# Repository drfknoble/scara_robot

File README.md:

# Selective Compliance Articulated Robot Arm (SCARA) Project

## Introduction

Welcome to my repository for my Selective Compliance Articulared Robot Arm (SCARA) project.

<!-- <div>

</div> -->

## Motivation

I started this project because commercial SCARA robots are very expensive and there any low-cost options for me to use in my teaching or research.

## Aims

The aims of this project included:
- Developing a low-cost, SCARA robot that can be used to teach students about mechatronics and robotics.

## Objectives

The objectives of this project included:
- Creating accessible Computer Aided Design (CAD) files.
- Creating accessible Electronics Design Automation (EDA) files.
- Creating accessible source code and software libraries.
- Creating an easy-to-assemble mobile robot that uses a microcontroller, stepper motors, and rotational sensors.

## Repository Structure

The repository is organised as follows:

```console
scara_project/         
    cad/                          
        fabrication/
        parts/
        sub_assemblies/   
    doc/                                   
    eda/
        manipulator_pcb/        
    src/
        esp32_program/
        my_bringup/
        my_scara_1_0_movit_config/
        my_scara_support/
```

All CAD files can be found in the `cad/` sub-directory. I used SolidWorks to create the 3D models of the robot's parts, sub-assemblies, and assembly. Files neeeded to fabricate the robot can be found in the `fabrication/` sub-directory.

All EDA files can be found in the `eda/` sub-directory. I used KiCAD to create the PCB for the robot. Files need to fabricate the PCB can be found in the `manipulator_pcb/` sub-directory.

All source code and software libaries are included in the `src/` sub-directory. I used an ESP32 as the robot's microcontroller and programmed it using PlatformIO's Arduino framework. The ESP32's source code can be found in the `esp32_program/` sub-directory. I also developed a ROS 2 package that makes use of ROS 2 Control and Moveit 2. The package's launch file can be found in the `my_bringup/` sub-directory. 

Documentation is included in the `doc/` sub-directory. I've included a Bill of Materaisl (BOM) file, which includes the compenents used.

## Tools Used

I used the following tools in this project:
- SOLIDWORKS.
- KiCAD.
- Microsoft Visual Studio Code and PlatforIO.
- ROS 2.

Get FreeCAD here: https://www.freecadweb.org/.  
Get KiCAD here: https://www.kicad.org/.  
Get Visual Studio Code here: https://code.visualstudio.com/.  
Get PlatforIO from here: https://platformio.org/. 

## Credit

Dr Frazer K. Noble  
http://drfknoble.com

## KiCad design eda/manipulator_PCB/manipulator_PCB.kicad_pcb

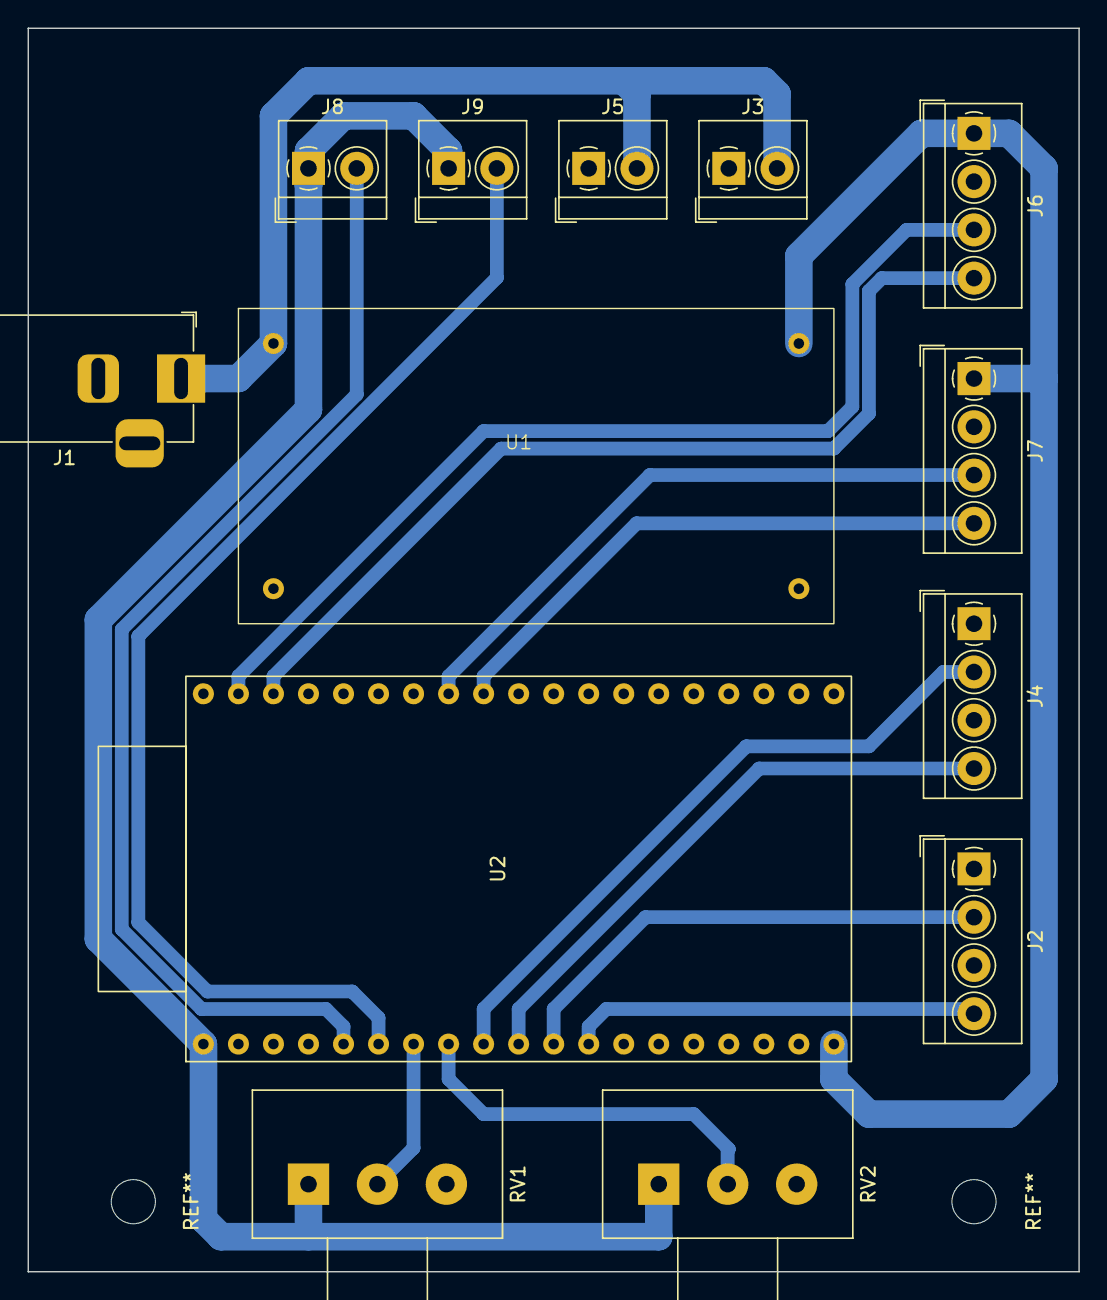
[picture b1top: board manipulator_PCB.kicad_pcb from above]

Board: 2 copper layers, 76.2 x 90.2 mm, 13 parts (0 on the bottom side), 16 nets.

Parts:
J1: Barrel_Jack_Switch_Pin3Ring; BarrelJack_Horizontal
J2, J4, J6, J7: Screw_Terminal_01x04; TerminalBlock_4Ucon_1x04_P3.50mm_Horizontal
J3, J5, J8, J9: Screw_Terminal_01x02; TerminalBlock_4Ucon_1x02_P3.50mm_Horizontal
RV1, RV2: 10K; Potentiometer_Alps_RK163_Single_Horizontal
U1: DC-DC_Converter
U2: ESP32-DevKitC

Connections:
+3V3: J8.1, J9.1, RV1.1, RV2.1, U2.1 (3V3)
+5V: J6.1, J7.1, U1.4 (VOUT+), U2.19 (5V0)
+12V: J1.1, J3.2, J5.2, U1.1 (VIN+)
DIR1: J2.2, U2.11 (27)
DIR2: J4.2, U2.9 (25)
GND: J1.2, J1.3, J2.1, J2.3, J3.1, J4.1, J4.3, J5.1, J6.2, J7.2, RV1.3, RV2.3, U1.2 (VIN-), U1.3 (VOUT-), U2.14 (GND), U2.32 (GND), U2.38 (GND)
unnamed: RV1.2, U2.7 (32)
unnamed: RV2.2, U2.8 (33)
SCL1: J6.4, U2.36 (22)
SCL2: J7.4, U2.30 (18)
SDA1: J6.3, U2.37 (23)
SDA2: J7.3, U2.31 (19)
STEP1: J2.4, U2.12 (14)
STEP2: J4.4, U2.10 (26)
lim1: J8.2, U2.5 (34)
lim2: J9.2, U2.6 (35)

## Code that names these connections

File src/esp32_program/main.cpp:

#include <Arduino.h>
#include <Wire.h>

// Configure I2C for joint 1 and 2's encoders.
TwoWire encoder1{ 0 }; // = TwoWire(0);
TwoWire encoder2{ 1 }; // = TwoWire(1);

/***
 * @brief. Defines GPIO pins and sets I/O state. 
 * 
 * @param. void.
 * @return void.
 */
void setup()
{
    encoder1.begin(GPIO_NUM_23, GPIO_NUM_22);
    encoder2.begin(GPIO_NUM_19, GPIO_NUM_18);
    
    // configure serial port.
    Serial.begin(115200);

    // Configure LEDs
    pinMode(GPIO_NUM_16, OUTPUT);
    digitalWrite(GPIO_NUM_16, HIGH);
    pinMode(GPIO_NUM_17, OUTPUT);
    digitalWrite(GPIO_NUM_17, HIGH);

    // Configure stepper 1
    // Direction pin 1 (dir1)
    pinMode(GPIO_NUM_27, OUTPUT);
    digitalWrite(GPIO_NUM_27, LOW);
    // Step pin 1 (step1)
    pinMode(GPIO_NUM_14, OUTPUT);
    digitalWrite(GPIO_NUM_14, LOW);

    // Configure stepper 2
    // Direction pin 2 (dir2)
    pinMode(GPIO_NUM_25, OUTPUT);
    digitalWrite(GPIO_NUM_25, LOW);
    // Step pin 2 (step2)
    pinMode(GPIO_NUM_26, OUTPUT);
    digitalWrite(GPIO_NUM_14, LOW);

    // configure analog inputs
    pinMode(GPIO_NUM_32, INPUT);
    pinMode(GPIO_NUM_33, INPUT);

}

/***
 * @brief. Reads and writes to GPIO pins.
 * 
 * @param. void.
 * @return. void.
*/
void loop()
{
    // Get data from analog inputs
    int analogInput1 = analogRead(GPIO_NUM_33);
    int analogInput2 = analogRead(GPIO_NUM_32);

    // Map analog value to joint limits
    float desiredAngle1 = (200 + 2700 * (float)analogInput1 / 4096);
    float desiredAngle2 = (1600 + 2200 * (float)analogInput2 / 4096);

    // Get angle from encoder 1
    encoder1.beginTransmission(0x36);
    encoder1.write(0x0E);
    encoder1.endTransmission();

    encoder1.requestFrom(0x36, 2);
    int data1 = encoder1.read();
    data1 <<= 8;
    data1 += encoder1.read();
    float angle1 = (float)data1;

    // Get angle from encoder 2
    encoder2.beginTransmission(0x36);
    encoder2.write(0x0E);
    encoder2.endTransmission();

    encoder2.requestFrom(0x36, 2);
    int data2 = encoder2.read();
    data2 <<= 8;
    data2 += encoder2.read();
    float angle2 = (float)data2;

    // Compute difference between set point and measured angle
    float error1 = desiredAngle1 - angle1;
    float error2 = desiredAngle2 - angle2;

    // A simple PID algorithm for joints 1 and 2
    if (error1 > +1.8 / 0.09) 
    {
        // angle is less than desired angle, move clockwise
        digitalWrite(GPIO_NUM_25, HIGH);
        digitalWrite(GPIO_NUM_26, HIGH);
        delay(10);
        digitalWrite(GPIO_NUM_26, LOW);
        delay(10);
        // angle1 = angle1 + 1.8;

    }
    else if (error1 < -1.8 / 0.09)
    {
        // angle is greater than desired angle, move anticlockwise
        digitalWrite(GPIO_NUM_25, LOW);
        digitalWrite(GPIO_NUM_26, HIGH);
        delay(10);
        digitalWrite(GPIO_NUM_26, LOW);
        delay(10);
        // angle1 = angle1 - 1.8;
    }

    if (error2 > +1.8 / 0.09) 
    {
        // angle is less than desired angle, move clockwise
        digitalWrite(GPIO_NUM_27, HIGH);
        digitalWrite(GPIO_NUM_14, HIGH);
        delay(10);
        digitalWrite(GPIO_NUM_14, LOW);
        delay(10);
        // Serial.println(angle1);
        // angle2 = angle2 + 1.8;

    }
    else if (error2 < -1.8 / 0.09)
    {
        // angle is greater than desired angle, move anticlockwise
        digitalWrite(GPIO_NUM_27, LOW);
        digitalWrite(GPIO_NUM_14, HIGH);
        delay(10);
        digitalWrite(GPIO_NUM_14, LOW);
        delay(10);
        // Serial.println(angle1);
        // angle2 = angle2 - 1.8;
    }


    char buf[100];
    sprintf(buf, "%f:%f:%f, %f:%f:%f", desiredAngle1, angle1, error1, desiredAngle2, angle2, error2);
    Serial.println(buf);

}

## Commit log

2023-10-07 Amended the README.md file.
2023-10-07 Updated comments to make use of doxygen style commenting.
